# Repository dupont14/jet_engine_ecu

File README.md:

# jet_engine_ecu
Collaboration space for WNE jet engine ECU

## Execution Plans
These are the execution plans being followed to perform the jet engine control systems task

### ECU Execution Plan

### Inlet PCB Execution Plan

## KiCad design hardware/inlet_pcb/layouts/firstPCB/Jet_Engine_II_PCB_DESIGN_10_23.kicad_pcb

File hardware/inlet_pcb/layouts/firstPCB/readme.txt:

This is the first pass at the Inlet PCB on KiCAD 8

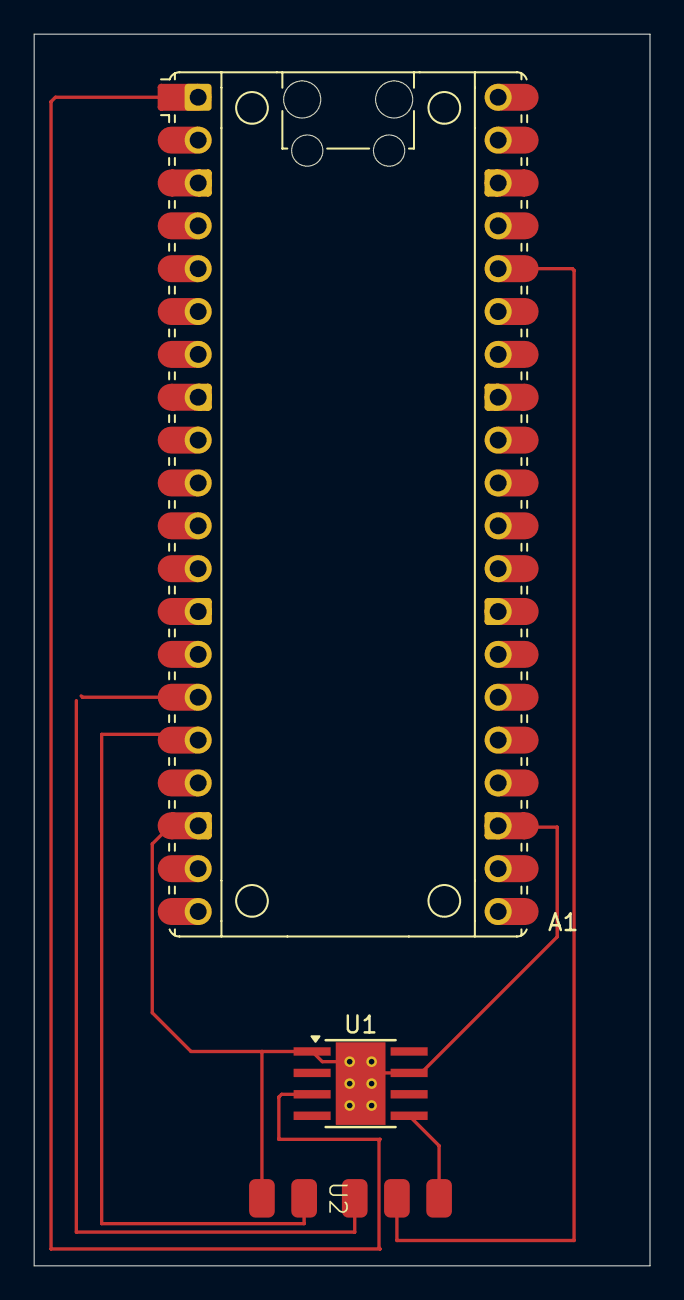
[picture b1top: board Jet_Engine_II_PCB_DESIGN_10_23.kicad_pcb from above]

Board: 2 copper layers, 36.5 x 73.0 mm, 3 parts (0 on the bottom side), 5 nets.

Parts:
A1: RaspberryPi_Pico; RaspberryPi_Pico_Common
U1: DRV8871DDA; Texas_HTSOP-8-1EP_3.9x4.9mm_P1.27mm_EP2.95x4.9mm_Mask2.4x3.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
U2: Inlet_PCB

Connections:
+3.3V: A1.36 (3V3), U2.2 (3.3V)
+10V: U1.5 (VM), U2.1 (10V)
GND: A1.3 (GND), A1.8 (GND), A1.13 (GND), A1.18 (GND), A1.23 (GND), A1.28 (GND), A1.38 (GND), U1.1 (GND), U1.7 (GND), U1.9 (GND), U2.5 (GND)
unnamed: A1.1 (GPIO0), U1.3 (IN1)
unnamed: A1.16 (GPIO12), U2.4 (RX)

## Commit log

2025-08-31 committing all readme
2025-09-10 Raspberry Pi Pico Datasheet
    Datasheet for Raspberry Pi Pico and Datasheet for the microcontroller ARM Cortex M0+ used on the Pico
2025-09-10 Raspberry Pi Pico Datasheet
    Includes Raspberry Pi Pico datasheet and the ARM Cortex M0+ microprocessor datasheet
    Link to Raspberry Pi Pico on Amazon: https://www.amazon.com/waveshare-Pico-Microcontroller-Development-High-Performance/dp/B08TVF499B/ref=sr_1_8?crid=ZJWKC1J7JZCC&dib=eyJ2IjoiMSJ9.EB-lb_YPIrKwllXlxQk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
2025-09-13 adding boot partition & interfaces file
2025-09-22 Create placeholder
2025-09-22 moving docs to datasheet
2025-09-23 adding 9/22 notes with action items for the next week
2025-09-23 Create README.md
    adding readme to datasheets
2025-09-23 Adding design review slides from 9/5 2025
    initial preliminary design review of FADEC
2025-09-24 Committing 9 24 meeting notes
2025-09-29 Added Raspberry Pi Pico pinout
2025-10-02 Committing meeting notes from oct 2nd Inlet PCB PDR
2025-10-06 committing execution plan
2025-10-06 Update README.md
    updating readme with execution plans
2025-10-06 Update README.md
    Inlet PCB execution plan added to readme
2025-10-08 Update cmdline.txt
    adding mac address to cmdline.txt
2025-10-20 Add meeting notes for Inlet PCB team on 10/20
    Documented meeting notes and action items for the Inlet PCB team, including member summaries and goals for the next sprint.
2025-10-20 Update meeting notes with action items
2025-10-24 Add initial readme for first PCB layout
2025-10-24 Files needed for KiCAD Schematic
2025-10-24 Add ReadMe.md for PCB Editor
2025-10-24 Raspberry Pi Pico Library for KiCAD
2025-10-24 DRV8871 H-Bridge Datasheet
2025-10-27 Frequency counter and PWM functions
2025-11-17 committing buildroot, hope ts works
2025-11-17 remove b
2025-11-17 again
2025-11-18 adding saved defconfig and overlay file directory fix
2025-11-21 idk what i am committing
2025-11-21 pushing actual defconfig
2025-12-21 Committing working ssh and some x11 stuff, remember to put ssh key in overlay/root/.ssh/authorized_keys
2025-12-21 committing boot configuration files and also the x_11 stuff
2026-01-16 Commit new config and initial x server script, trying to get to work with windows
2026-01-27 adding a bunch of shit
2026-01-27 committing a few more things
2026-01-27 committing new kernel and defconfig
